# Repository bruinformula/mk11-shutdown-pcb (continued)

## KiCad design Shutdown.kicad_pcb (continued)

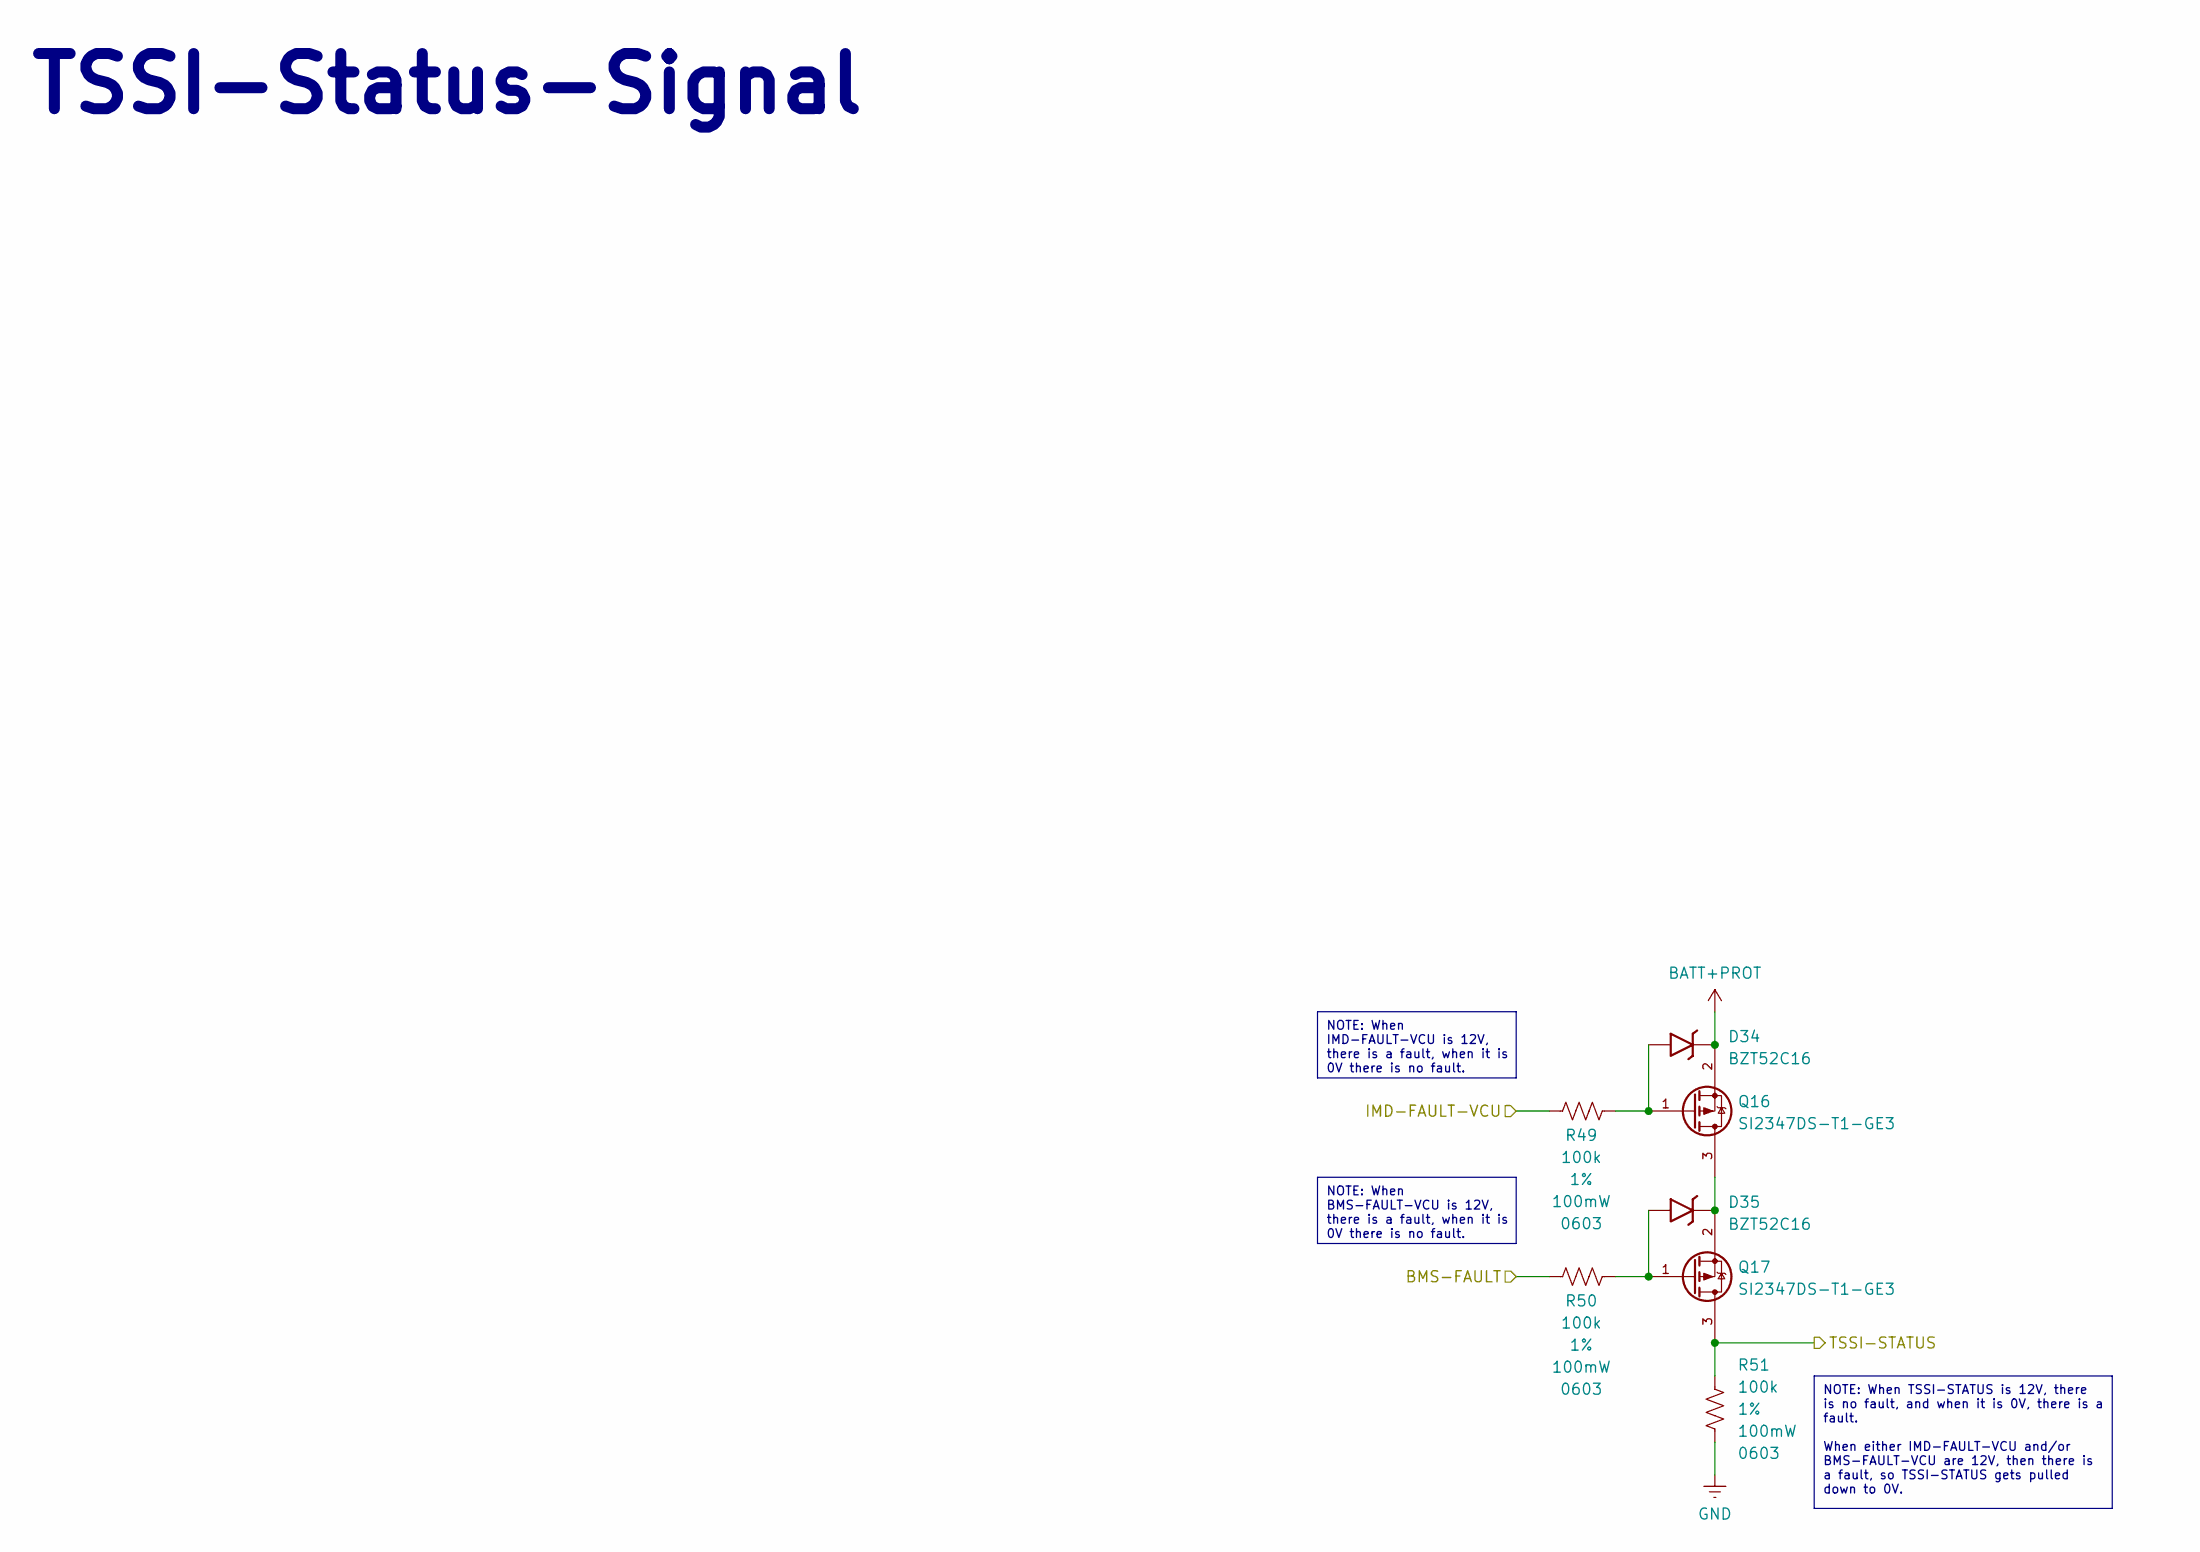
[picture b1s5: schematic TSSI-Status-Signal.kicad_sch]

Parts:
D34, D35: BZT52C16; D_SOD-123; Manufacturer P/N BZT52C16; Digikey P/N 4878-BZT52C16CT-ND
Q16, Q17: SI2347DS-T1-GE3; SOT-23-3; Manufacturer P/N SI2347DS-T1-GE3; Digikey P/N SI2347DS-T1-GE3CT-ND
R49, R50, R51: 100k; R_0603_1608Metric_Pad0.98x0.95mm_HandSolder; Tolerance 1%; Power Rating 100mW; Manufacturer P/N 0603WAF1003T5E; Digikey P/N RG16P100KBCT-ND

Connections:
/BMS-FAULT: R50.1; also elsewhere on the board
/IMD-FAULT-VCU: R49.1; also elsewhere on the board
/TSSI-STATUS: Q17.3 (D), R51.2; also elsewhere on the board
BATT+PROT: D34.1 (K), Q16.2 (S); also elsewhere on the board
GND: R51.1; also elsewhere on the board
unnamed: D34.2 (A), Q16.1 (G), R49.2
unnamed: D35.2 (A), Q17.1 (G), R50.2
unnamed: D35.1 (K), Q16.3 (D), Q17.2 (S)

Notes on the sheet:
TSSI-Status-Signal
NOTE: When IMD-FAULT-VCU is 12V, there is a fault, when it is 0V there is no fault.
NOTE: When TSSI-STATUS is 12V, there is no fault, and when it is 0V, there is a fault. When either IMD-FAULT-VCU and/or BMS-FAULT-VCU are 12V, then there is a fault, so TSSI-STATUS gets pulled down to 0V.
NOTE: When BMS-FAULT-VCU is 12V, there is a fault, when it is 0V there is no fault.

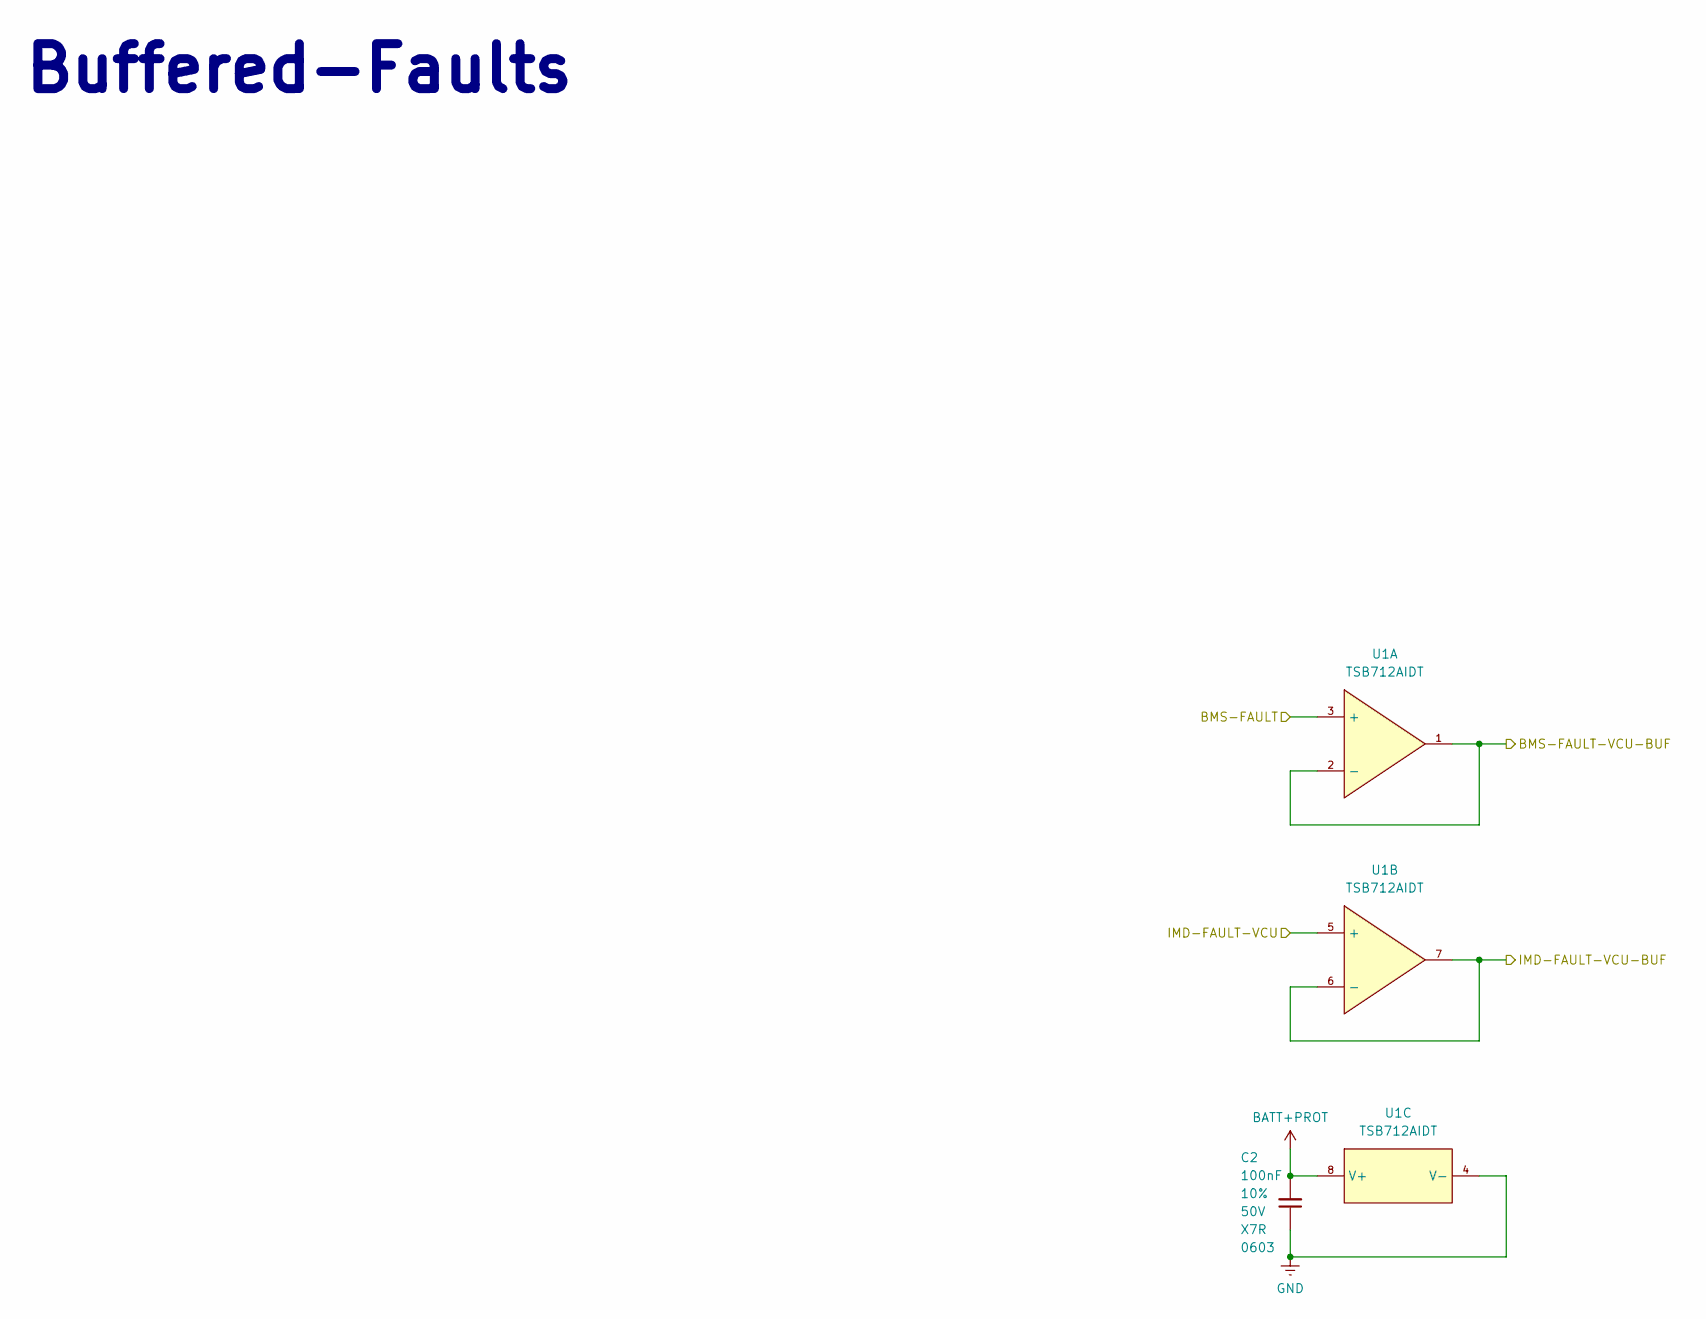
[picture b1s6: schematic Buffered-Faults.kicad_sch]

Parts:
C2: 100nF; C_0603_1608Metric_Pad1.08x0.95mm_HandSolder; Tolerance 10%; Voltage 50V; Manufacturer P/N CC0603KRX7R9BB104; Digikey P/N 311-1344-1-ND
U1: TSB712AIDT; SOIC-8_5.3x5.3mm_P1.27mm; Manufacturer P/N TSB712AIDT; Digikey P/N 497-19067-1-ND

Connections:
/BMS-FAULT: U1.3 (+); also elsewhere on the board
/BMS-FAULT-VCU-BUF: U1.1, U1.2 (-); also elsewhere on the board
/IMD-FAULT-VCU: U1.5 (+); also elsewhere on the board
/IMD-FAULT-VCU-BUF: U1.6 (-), U1.7; also elsewhere on the board
BATT+PROT: C2.2, U1.8 (V+); also elsewhere on the board
GND: C2.1, U1.4 (V-); also elsewhere on the board

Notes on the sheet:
Buffered-Faults

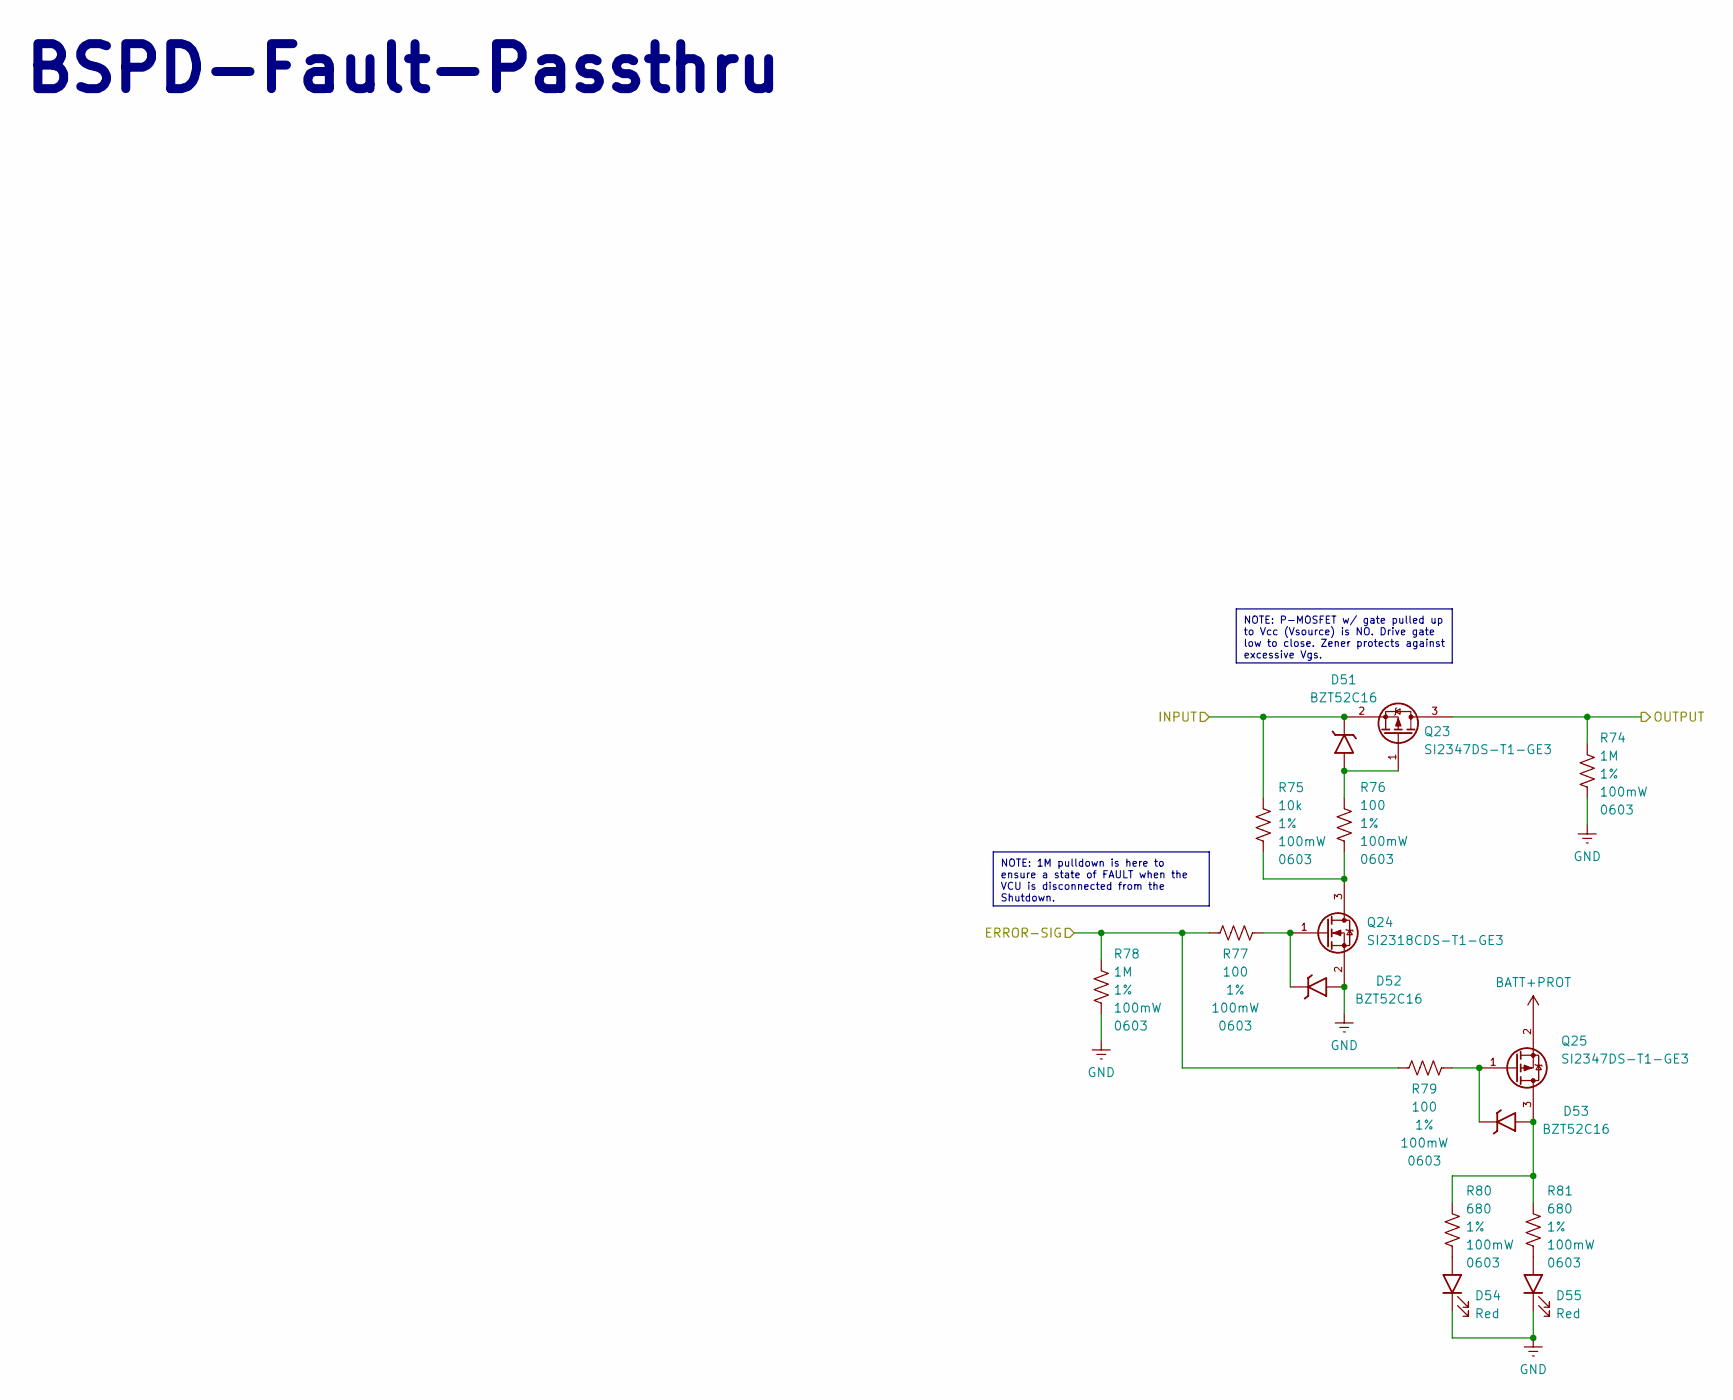
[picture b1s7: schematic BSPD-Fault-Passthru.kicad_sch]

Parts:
D51, D52, D53: BZT52C16; D_SOD-123; Manufacturer P/N BZT52C16; Digikey P/N 4878-BZT52C16CT-ND
D54, D55: Red; LED_0805_2012Metric; Manufacturer P/N NCD0805R1; Digikey P/N 160-1427-1-ND
Q23, Q25: SI2347DS-T1-GE3; SOT-23-3; Manufacturer P/N SI2347DS-T1-GE3; Digikey P/N SI2347DS-T1-GE3CT-ND
Q24: SI2318CDS-T1-GE3; SOT-23-3; Manufacturer P/N SI2318CDS-T1-GE3; Digikey P/N SI2318CDS-T1-GE3CT-ND
R74, R78: 1M; R_0603_1608Metric_Pad0.98x0.95mm_HandSolder; Tolerance 1%; Power Rating 100mW; Manufacturer P/N 0603WAF1004T5E; Digikey P/N YAG4498CT-ND
R75: 10k; R_0603_1608Metric_Pad0.98x0.95mm_HandSolder; Tolerance 1%; Power Rating 100mW; Manufacturer P/N 0603WAF1002T5E; Digikey P/N 541-10.0KHCT-ND
R76, R77, R79: 100; R_0603_1608Metric_Pad0.98x0.95mm_HandSolder; Tolerance 1%; Power Rating 100mW; Manufacturer P/N 0603WAF1000T5E; Digikey P/N 311-100HRCT-ND
R80, R81: 680; R_0603_1608Metric_Pad0.98x0.95mm_HandSolder; Tolerance 1%; Power Rating 100mW; Manufacturer P/N 0603WAF6800T5E; Digikey P/N 311-680GRCT-ND

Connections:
/BMS-Fault-Passthru/INPUT: Q23.3 (D), R74.2; also elsewhere on the board
/BSPD-FAULT-VCU: R77.1, R78.2, R79.1; also elsewhere on the board
BATT+PROT: D51.1 (K), Q23.2 (S), Q25.2 (S), R75.2; also elsewhere on the board
GND: D52.2 (A), D54.1 (K), D55.1 (K), Q24.2 (S), R74.1, R78.1; also elsewhere on the board
unnamed: D51.2 (A), Q23.1 (G), R76.2
unnamed: D52.1 (K), Q24.1 (G), R77.2
unnamed: D53.2 (A), Q25.3 (D), R80.2, R81.2
unnamed: D53.1 (K), Q25.1 (G), R79.2
unnamed: D54.2 (A), R80.1
unnamed: D55.2 (A), R81.1
unnamed: Q24.3 (D), R75.1, R76.1

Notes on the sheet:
BSPD-Fault-Passthru
NOTE: P-MOSFET w/ gate pulled up to Vcc (Vsource) is NO. Drive gate low to close. Zener protects against excessive Vgs.
NOTE: 1M pulldown is here to ensure a state of FAULT when the VCU is disconnected from the Shutdown.

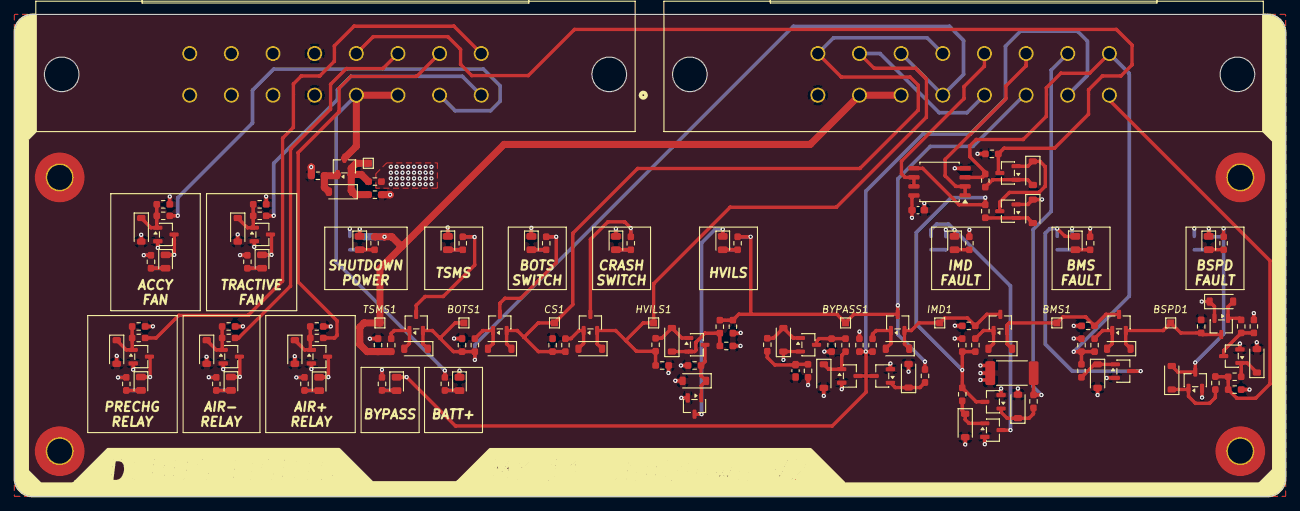
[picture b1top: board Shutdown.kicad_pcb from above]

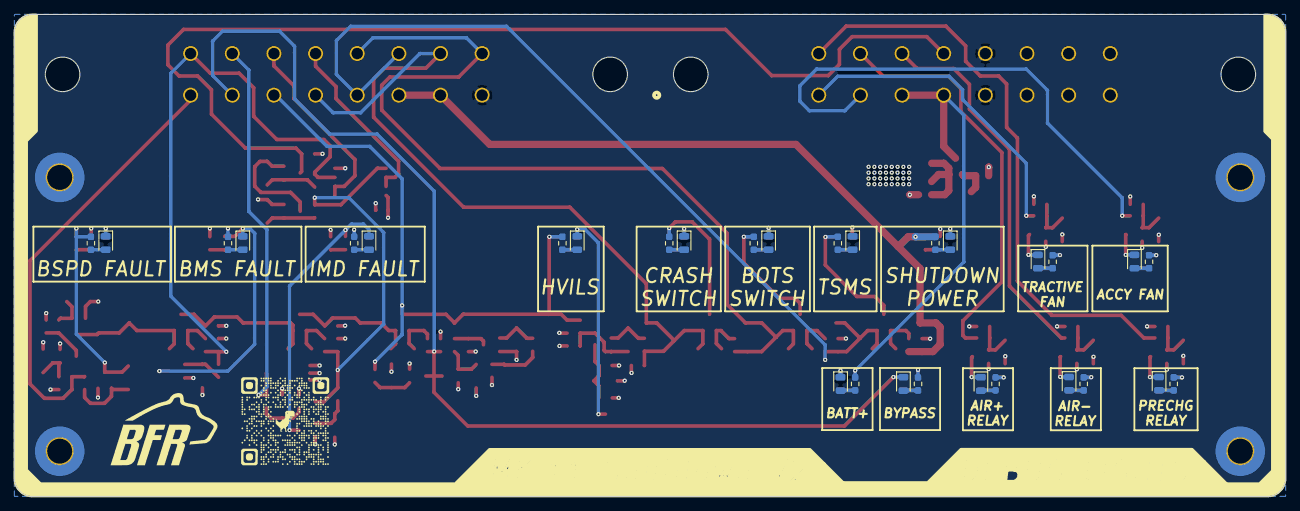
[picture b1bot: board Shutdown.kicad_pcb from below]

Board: 4 copper layers, 178.3 x 67.6 mm, 179 parts (30 on the bottom side), 97 nets.

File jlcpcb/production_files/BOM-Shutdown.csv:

Comment,Designator,Footprint,LCSC,Quantity
0,R1,R_0603_1608Metric_Pad0.98x0.95mm_HandSolder,C21189,1
0194270049,"J1,J2",0194270049,C17549932,2
100,"R7,R76,R77,R79",R_0603_1608Metric_Pad0.98x0.95mm_HandSolder,C22775,4
100k,"R10,R11,R2,R23,R24,R4,R40,R41,R42,R46,R47,R48,R49,R5,R50,R51,R52,R56,R57,R58,R59,R6,R61,R62,R63,R73,R9",R_0603_1608Metric_Pad0.98x0.95mm_HandSolder,C25803,27
100nF,C2,C_0603_1608Metric_Pad1.08x0.95mm_HandSolder,C14663,1
10k,"R3,R34,R35,R36,R53,R64,R75",R_0603_1608Metric_Pad0.98x0.95mm_HandSolder,C25804,7
13k,R60,R_0603_1608Metric_Pad0.98x0.95mm_HandSolder,C22797,1
1M,"R37,R43,R74,R78",R_0603_1608Metric_Pad0.98x0.95mm_HandSolder,C22935,4
2.2k,R8,R_2512_6332Metric_Pad1.40x3.35mm_HandSolder,C2934099,1
22,"R21,R22,R31,R32,R33",R_0603_1608Metric_Pad0.98x0.95mm_HandSolder,C23345,5
3.6k,"R54,R55",R_0603_1608Metric_Pad0.98x0.95mm_HandSolder,C22980,2
390k,R12,R_0603_1608Metric_Pad0.98x0.95mm_HandSolder,C23150,1
470nF,C1,C_0603_1608Metric_Pad1.08x0.95mm_HandSolder,C1623,1
560,"R25,R26,R27,R28,R29,R30",R_0603_1608Metric_Pad0.98x0.95mm_HandSolder,C23204,6
6.8k,"R13,R14,R15,R16",R_0603_1608Metric_Pad0.98x0.95mm_HandSolder,C23212,4
680,"R17,R18,R19,R20,R38,R39,R44,R45,R65,R66,R67,R68,R69,R70,R71,R72,R80,R81",R_0603_1608Metric_Pad0.98x0.95mm_HandSolder,C23228,18
BZT52C16,"D1,D15,D16,D2,D23,D24,D25,D26,D29,D3,D30,D33,D34,D35,D36,D37,D38,D39,D4,D5,D50,D51,D52,D53,D6",D_SOD-123,C2105,25
Blue,"D17,D18,D19,D20,D21,D22",LED_0805_2012Metric,C84259,6
Green,"D40,D41",LED_0805_2012Metric,C84260,2
Red,"D11,D12,D13,D14,D27,D28,D31,D32,D42,D43,D44,D45,D46,D47,D48,D49,D54,D55",LED_0805_2012Metric,C84256,18
SI2318CDS-T1-GE3,"Q10,Q11,Q13,Q15,Q22,Q24,Q3,Q4,Q5,Q7,Q8,Q9",SOT-23-3,C14498,12
SI2347DS-T1-GE3,"Q1,Q12,Q14,Q16,Q17,Q18,Q19,Q2,Q20,Q21,Q23,Q25,Q6",SOT-23-3,C145002,13
TSB712AIDT,U1,SOIC-8_5.3x5.3mm_P1.27mm,C2058811,1
White,"D10,D7,D8,D9",LED_0805_2012Metric,C34499,4
~,MH2,MountingHole_3.5mm_Pad_TopBottom,,1
BOTS,BOTS1,TestPoint_Pad_1.0x1.0mm,,1
CS,CS1,TestPoint_Pad_1.0x1.0mm,,1
~,MH1,MountingHole_3.5mm_Pad_TopBottom,,1
~,BMS1,TestPoint_Pad_1.0x1.0mm,,1
~,BSPD1,TestPoint_Pad_1.0x1.0mm,,1
~,VIN1,TestPoint_Pad_1.0x1.0mm,,1
HVILS,HVILS1,TestPoint_Pad_1.0x1.0mm,,1
TSMS,TSMS1,TestPoint_Pad_1.0x1.0mm,,1
~,MH3,MountingHole_3.5mm_Pad_TopBottom,,1
~,IMD1,TestPoint_Pad_1.0x1.0mm,,1
~,BYPASS1,TestPoint_Pad_1.0x1.0mm,,1
~,MH4,MountingHole_3.5mm_Pad_TopBottom,,1

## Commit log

2025-07-14 initial commit, mk10 shutdown but with updated schematics and added notes, same PCB
2025-10-08 completed schematic cleanup, back on 12V
2025-10-08 test push
2025-10-09 another test
2025-10-09 i think it worked
2025-10-15 completed placement:
2025-10-15 pushing to see slack notif
2026-02-07 changed BSPD, BMS fault logic to match Mk11 specs, all signals going back to VCU have 12V fault, 0V no fault readings, connector symbols/footprints left for next push
2026-02-07 nvm bms and imd are 12V fault, 0V no fault, only BSPD is 12V no fault, 0V fault going back to vcu rn
2026-02-10 maintenance push
2026-02-10 added comments to TSSI light sheet
2026-02-11 added in second connector for power, SD power, debug
2026-02-11 cleaning port names
2026-02-11 updating component properties
2026-02-11 updated port directionalities, updated pinout
2026-02-13 Schem is reannotated time to redo all of the layout
2026-02-13 Finished shutdown, 0 drc, need to export gerbers
2026-02-13 EXPORTED Gerbers, fixed qr code
2026-02-13 fixed silk and re-exported
2026-05-03 added comments to add that for future revs there should be a pulldown between shutdown fault passthru stages
2026-05-11 schematic updated to V2 extra crispy
2026-05-12 layout done extra crispy v2
2026-05-12 rounded corners
2026-05-12 Exported Gerbers
